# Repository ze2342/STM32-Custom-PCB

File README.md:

# STM32 Custom PCB Design

A custom STM32-based embedded system PCB designed in KiCad following professional PCB design practices inspired by Phil’s Lab.

## Overview

This project demonstrates the complete workflow of designing a professional embedded STM32 PCB from scratch instead of using ready-made development boards like the STM32 Blue Pill.

The PCB was designed with focus on:
- Clean routing
- Ground plane implementation
- Proper power distribution
- Compact embedded hardware layout
- Professional PCB engineering workflow

---

## Features

- STM32 microcontroller
- USB interface
- SWD programming/debugging header
- UART communication header
- BOOT mode switch
- I2C header
- Ground plane implementation
- Mounting holes
- Fully clean DRC
  - 0 Errors
  - 0 Warnings

---

## Tools Used

- KiCad
- STM32
- Git & GitHub

---

## PCB Preview

### Schematic

### PCB Layout

### 3D View

## Learning Outcomes

Through this project I learned:

- STM32 hardware design
- PCB routing techniques
- Ground plane usage
- Design Rule Check (DRC)
- Via sizing and routing
- Footprint customization
- USB and UART interfacing
- Embedded hardware workflow
- GitHub project management

---

## Folder Structure

```text
STM32-CUSTOM-BOARD/
│
├── KiCad/
├── Images/
├── README.md
└── LICENSE
```

---

## Future Improvements

- Add more GPIO breakout headers
- Add onboard sensors
- Add firmware examples
- Create a custom enclosure
- Add power protection circuitry

---

## Inspiration

This project was inspired by Phil’s Lab embedded hardware and PCB design tutorials.

---

## Author

Zeeshan Ahmad

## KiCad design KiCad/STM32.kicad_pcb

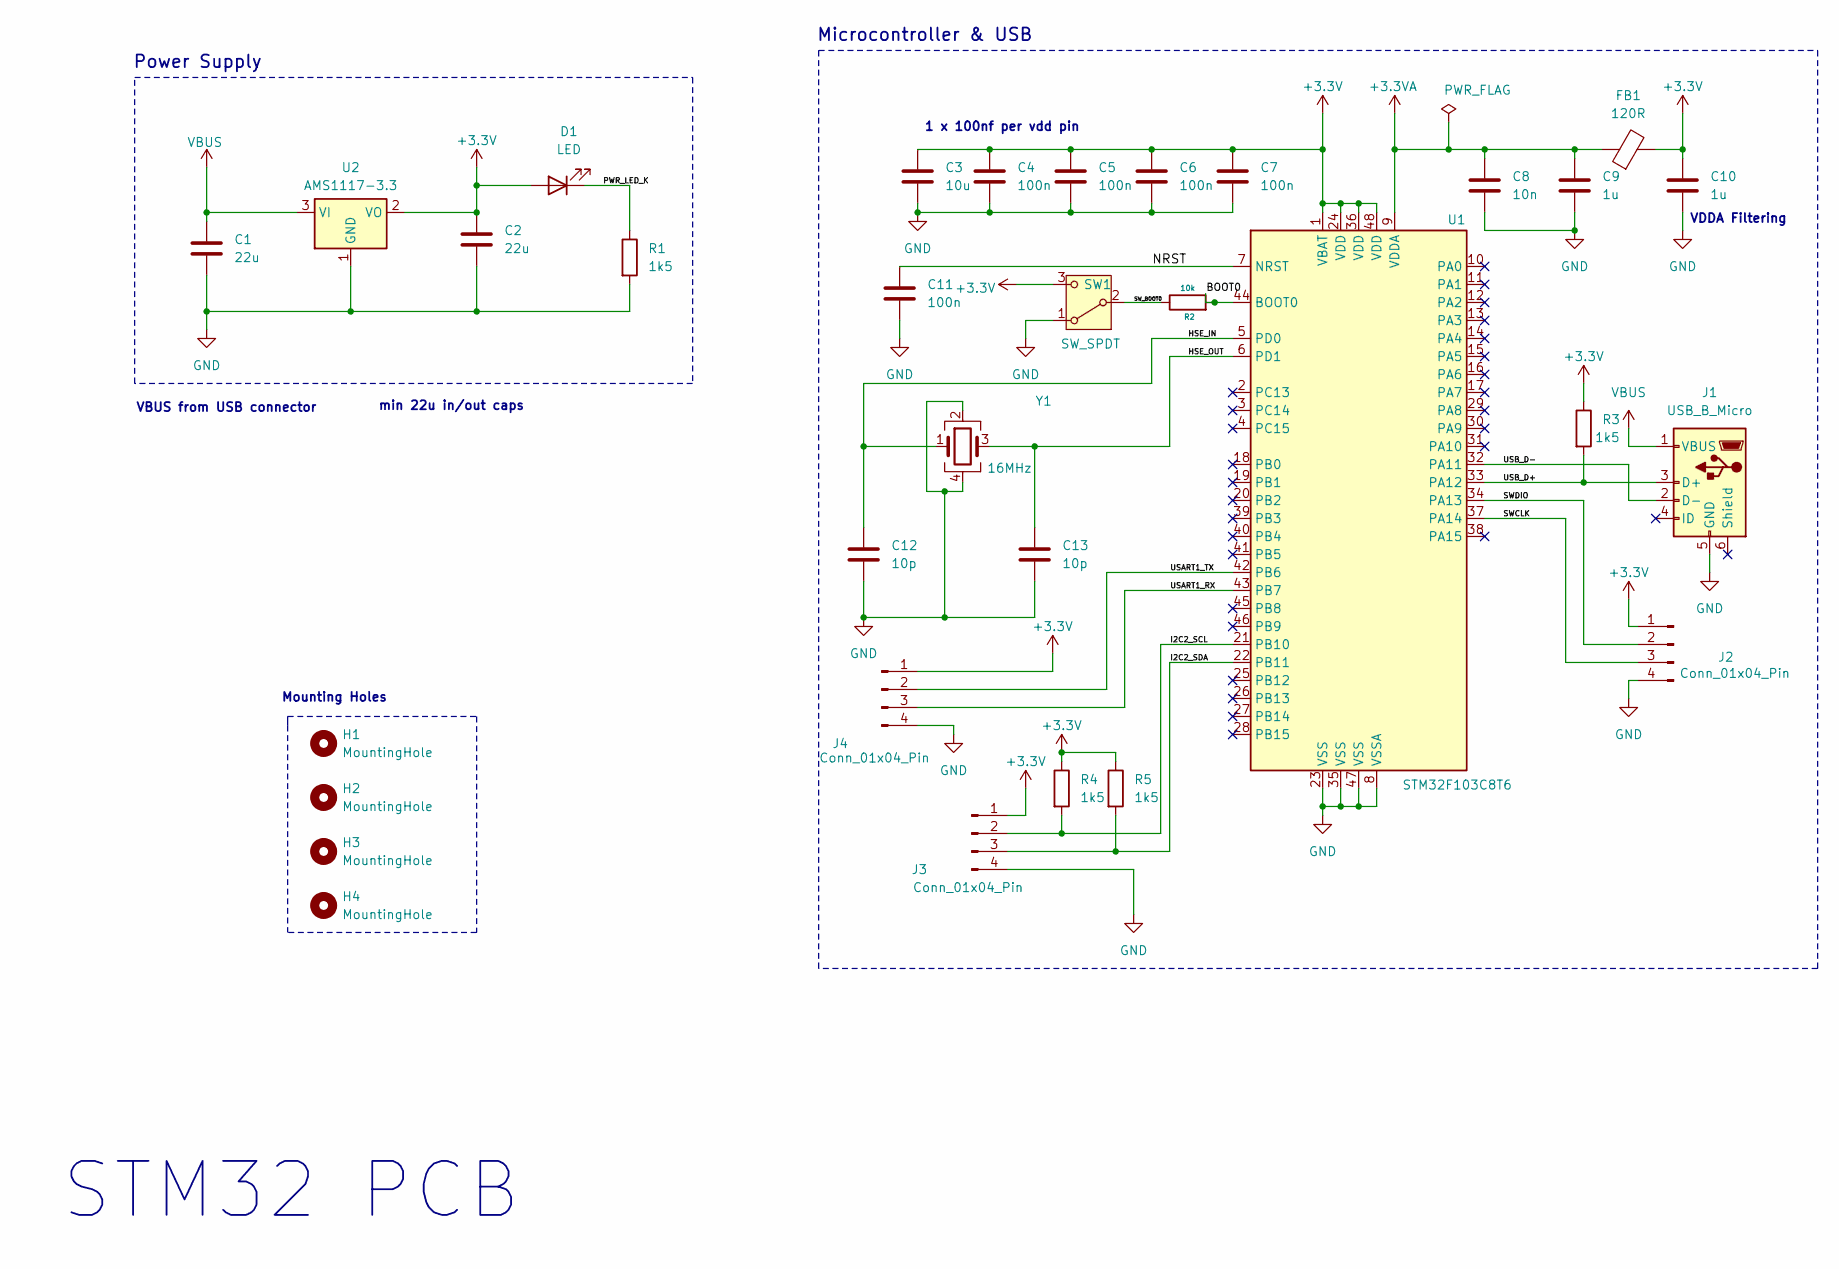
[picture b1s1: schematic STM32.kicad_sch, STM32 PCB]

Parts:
C1, C2: 22u; C_0805_2012Metric
C3: 10u; C_0603_1608Metric
C4, C5, C6, C7, C11: 100n; C_0402_1005Metric
C8: 10n; C_0402_1005Metric
C9, C10: 1u; C_0402_1005Metric
C12, C13: 10p; C_0402_1005Metric
D1: LED; LED_0603_1608Metric
FB1: 120R; L_0603_1608Metric
H1, H2, H3, H4: MountingHole; MountingHole_2.2mm_M2
J1: USB_B_Micro; USB_Micro-B_Wuerth_629105150521
J2, J3, J4: Conn_01x04_Pin; PinHeader_1x04_P2.54mm_Vertical
R1, R3, R4, R5: 1k5; R_0402_1005Metric
R2: 10k; R_0402_1005Metric
SW1: SW_SPDT; SW_SPDT_PCM12
U1: STM32F103C8T6; LQFP-48_7x7mm_P0.5mm
U2: AMS1117-3.3; SOT-223-3_TabPin2
Y1: 16MHz; Crystal_SMD_3225-4Pin_3.2x2.5mm

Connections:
+3.3V: C2.1, C3.1, C4.1, C5.1, C6.1, C7.1, C10.1, D1.2 (A), FB1.2, J2.1, J3.1, J4.1, R3.1, R4.1, R5.1, SW1.3 (C), U1.1 (VBAT), U1.24 (VDD), U1.36 (VDD), U1.48 (VDD), U2.2 (VO)
+3.3VA: C8.1, C9.1, FB1.1, U1.9 (VDDA)
/BOOT0: R2.2, U1.44 (BOOT0)
/HSE_IN: C12.1, U1.5 (PD0), Y1.1
/HSE_OUT: C13.1, U1.6 (PD1), Y1.3
/I2C2_SCL: J3.2, R4.2, U1.21 (PB10)
/I2C2_SDA: J3.3, R5.2, U1.22 (PB11)
/NRST: C11.1, U1.7 (NRST)
/PWR_LED_K: D1.1 (K), R1.1
/SWCLK: J2.3, U1.37 (PA14)
/SWDIO: J2.2, U1.34 (PA13)
/SW_BOOT0: R2.1, SW1.2 (B)
/USART1_RX: J4.3, U1.43 (PB7)
/USART1_TX: J4.2, U1.42 (PB6)
/USB_D+: J1.3 (D+), R3.2, U1.33 (PA12)
/USB_D-: J1.2 (D-), U1.32 (PA11)
GND: C1.2, C2.2, C3.2, C4.2, C5.2, C6.2, C7.2, C8.2, C9.2, C10.2, C11.2, C12.2, C13.2, J1.5 (GND), J2.4, J3.4, J4.4, R1.2, SW1.1 (A), U1.8 (VSSA), U1.23 (VSS), U1.35 (VSS), U1.47 (VSS), U2.1 (GND), Y1.2, Y1.4
VBUS: C1.1, J1.1 (VBUS), U2.3 (VI)

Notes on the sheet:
Mounting Holes
STM32 PCB
VDDA Filtering
VBUS from USB connector
1 x 100nf per vdd pin
min 22u in/out caps
Microcontroller & USB
Power Supply

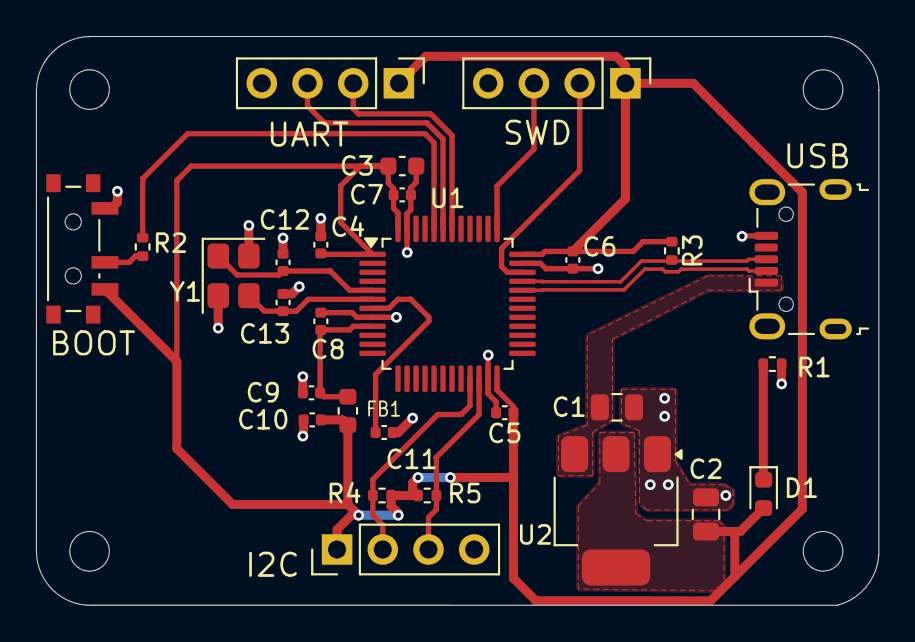
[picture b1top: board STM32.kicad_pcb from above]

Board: 2 copper layers, 46.8 x 31.6 mm, 32 parts (0 on the bottom side), 18 nets.
